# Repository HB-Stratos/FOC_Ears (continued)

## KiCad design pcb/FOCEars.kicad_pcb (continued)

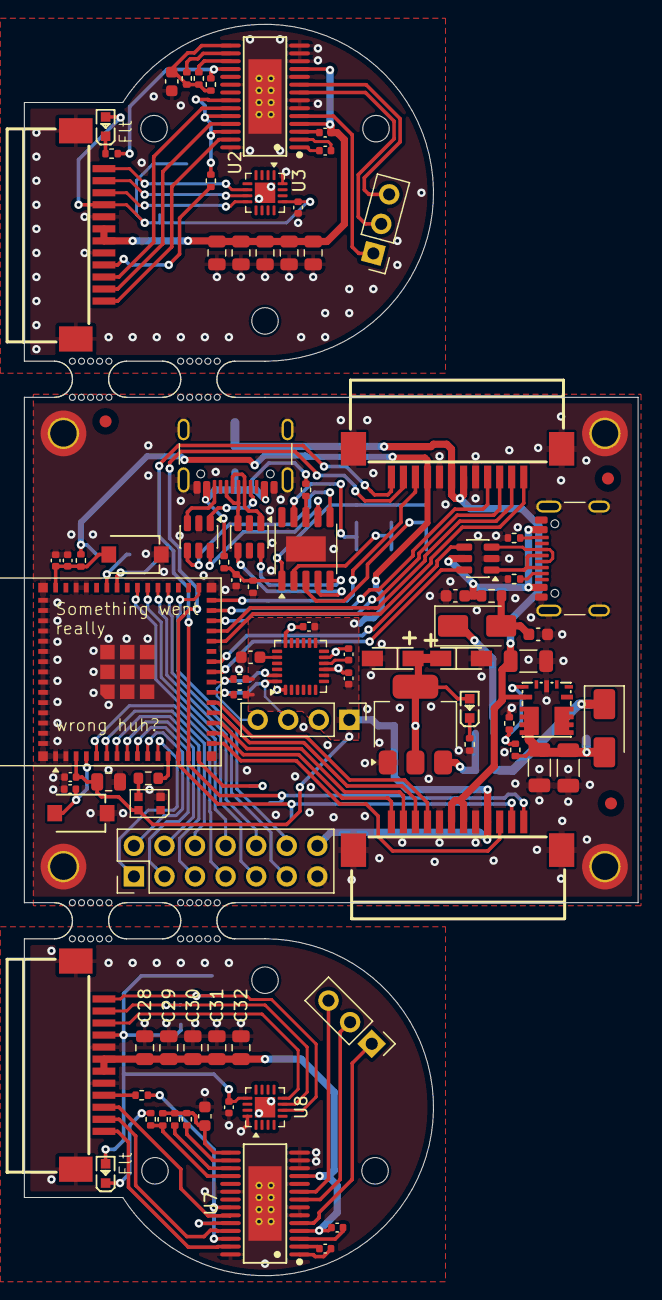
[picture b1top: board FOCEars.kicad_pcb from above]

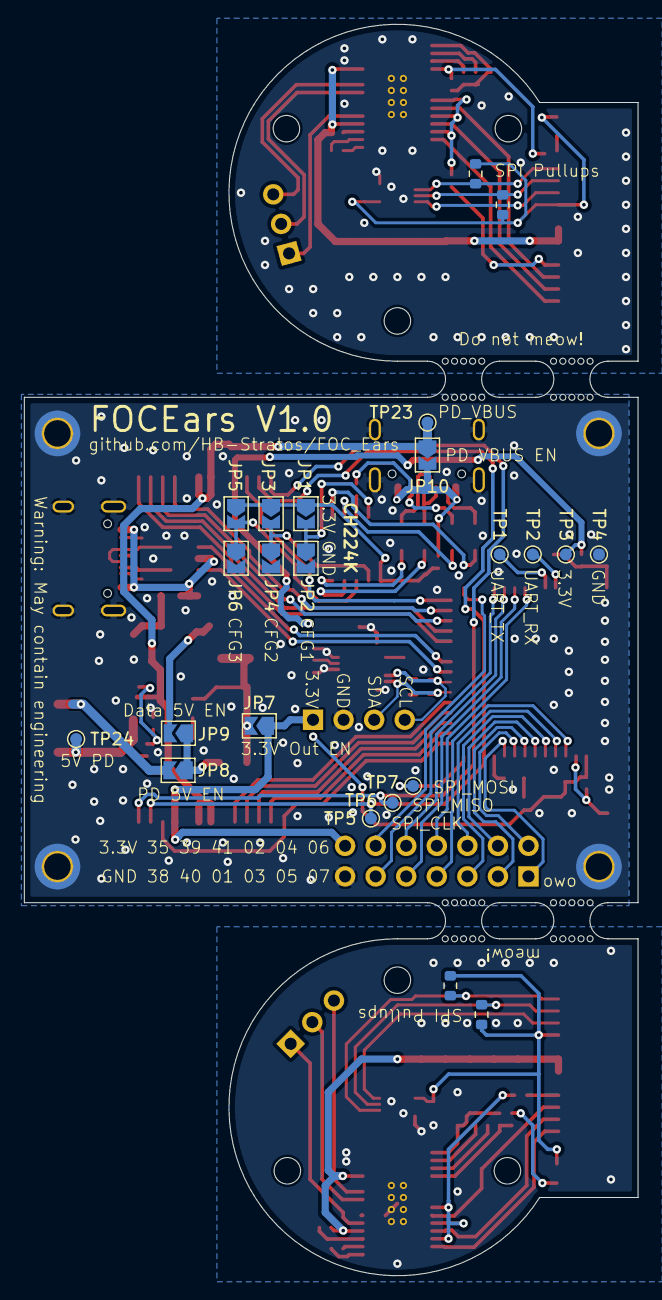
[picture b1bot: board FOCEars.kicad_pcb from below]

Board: 2 copper layers, 51.0 x 104.0 mm, 128 parts (23 on the bottom side), 111 nets.

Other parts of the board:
mouse-bite-3mm-slot, mouse-bite-3mm-slot#2, mouse-bite-3mm-slot#3, mouse-bite-3mm-slot#4: VAL**; mouse-bite-3mm-slot

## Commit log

2025-06-18 initial commit, sorry it's big
2025-06-18 update filter plotter still broken
2025-06-18 implement basic motion reactance
2025-06-18 working ear flicks
2025-06-18 made button toggle
2025-07-20 (finally) wrote some documentation
2025-07-20 Fix docs formatting
2025-07-20 Fix yet more docs formatting errors
2025-07-20 Add Build Env Setup instructions
2025-07-20 Add LICENSE
2025-11-27 Large commit, major restructuring, a few test files. Switch platformio envs to compile the various test scripts.
2025-11-28 Clean up and fix PlatformIO, CDC now works!
2025-12-03 Remove useless directories.
2025-12-23 A few more test scripts to debug calibration
2025-12-23 Add PCB files
2025-12-23 Update Readme with notes for congress
